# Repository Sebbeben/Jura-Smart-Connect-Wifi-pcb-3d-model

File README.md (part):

# Jura-Smart-Connect-Wifi-pcb-3d-model
Here i will try to make my own pcb and housing to work with my Jura E60 coffe maker

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
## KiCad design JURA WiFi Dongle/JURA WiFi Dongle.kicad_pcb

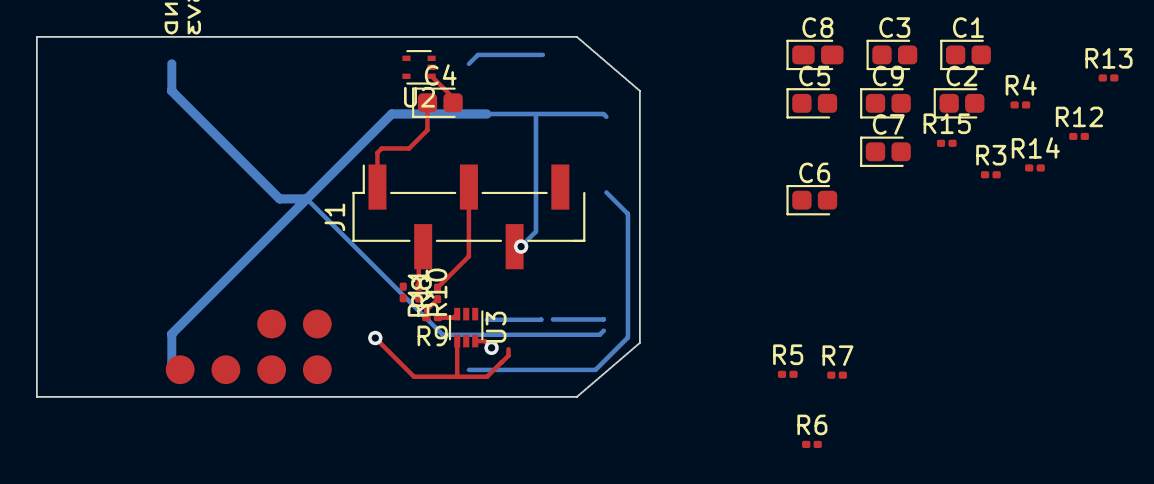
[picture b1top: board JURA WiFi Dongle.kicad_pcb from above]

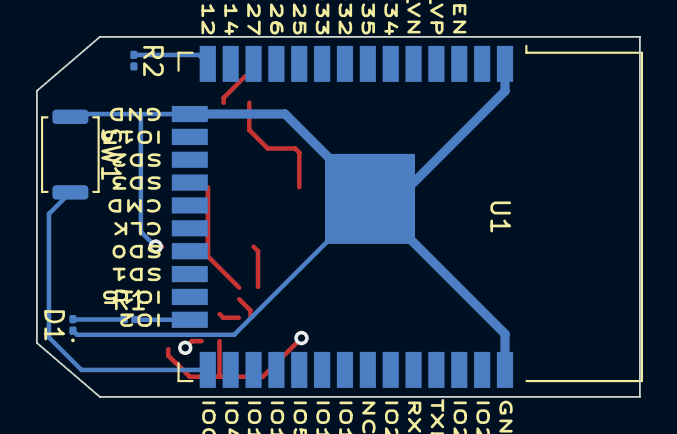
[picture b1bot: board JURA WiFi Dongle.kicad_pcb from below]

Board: 2 copper layers, 33.5 x 20.0 mm, 30 parts (5 on the bottom side), 16 nets.

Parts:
C1, C2, C3, C4, C5, C7, C9: C; CP_EIA-1608-08_AVX-J
C6: 480uF; CP_EIA-1608-08_AVX-J
C8: C; CP_EIA-1608-08_AVX-J_Pad1.25x1.05mm_HandSolder
D1: TSAL4400; LED_0201_0603Metric
J1: Conn_01x05_MountingPin; PinHeader_1x05_P2.54mm_Vertical_SMD_Pin1Right
R1, R8, R9: 100; R_0201_0603Metric
R2: 7.4K; R_0201_0603Metric
R3: 131,7K; R_0201_0603Metric
R4: 3,9K; R_0201_0603Metric
R5: 1K; R_0201_0603Metric
R6: 2K; R_0201_0603Metric
R7, R10, R11: 0; R_0201_0603Metric
R12: 8,4 K; R_0201_0603Metric
R13, R14, R15: 10K; R_0201_0603Metric
SW1: SW_Push; SW_Push_SPST_NO_Alps_SKRK
U1: ESP32-WROOM-32D; ESP32-WROOM-32
U2: GL2576-5.0TA5R; SOT-553
U3: ICL7667; SOT-563

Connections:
3V3: C1.1, C3.2, C6.2, C7.2, C8.1, R3.2, R8.1, R12.1, R13.2, R14.2, R15.1, U1.2 (VDD), U3.6 (V+)
?: R9.1, U3.3 (V-)
GND: C2.1, C5.1, C6.1, C9.2, D1.1 (K), J1.4, R2.2, R4.1, R6.1, R14.1, SW1.1, U1.1 (GND), U1.15 (GND), U1.38 (GND), U1.39 (GND), U2.2 (OUT), U3.4 (INB)
NC: J1.2, R10.1
unnamed: C1.2, R3.1, R4.2
unnamed: C2.2, U2.4 (FB)
unnamed: C4.2, U2.1 (VIN)
unnamed: C5.2, U3.2 (INA)
unnamed: C7.1, R15.2
unnamed: C8.2, C9.1
unnamed: D1.2 (A), R1.1
unnamed: R5.2, R6.2, R7.1
unnamed: R9.2, R11.1
unnamed: R12.2, U3.5 (~OUTB)
RxD: J1.3, U1.34 (RXD0/IO3)
TxD: J1.5, U1.35 (TXD0/IO1)

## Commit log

2024-12-16 Upload of Jura WiFi Connect Original firmware
    backup of firmware, original jura wifi connect.
2025-05-16 Update README.md
    adding pcb layout
2025-05-17 Update README.md
    restore to before, HTML to Markdown did not work as expected

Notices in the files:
README.md:
er { padding: 0; } /\* #bomhead { position: sticky; top: 0px; z-index: 1; } \*/ /////////////////////////////////////////////// /\* Split.js - v1.3.5 MIT License https://github.com/nathancahill/Split.js \*/ !function(e,t){"object"==typeof exports&&"undefined"!=typeof module?module.exports=t():"funct
